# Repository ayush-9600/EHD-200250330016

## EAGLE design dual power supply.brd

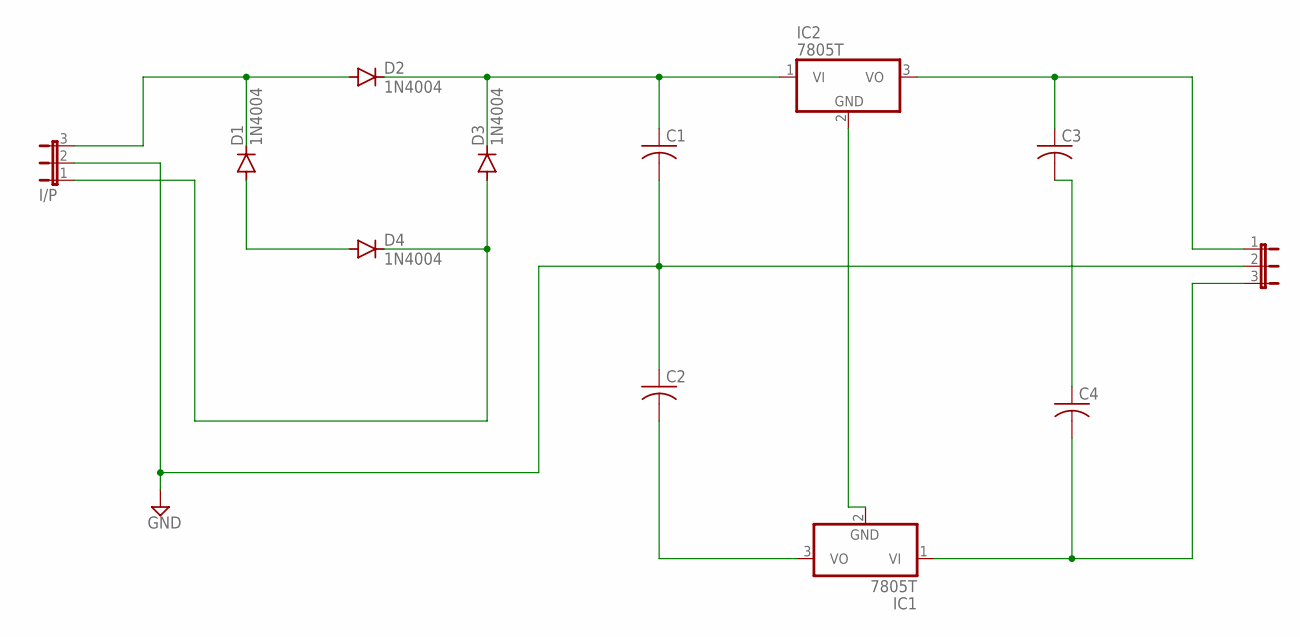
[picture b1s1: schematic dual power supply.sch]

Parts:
C1, C2, C3, C4: C-US025-024X044; C025-024X044
D1, D2, D3, D4: 1N4004; DO41-10
I/P: JP2E; JP2
IC1, IC2: 7805T; TO220H
O/P: JP2E; JP2

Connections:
GND: C1.2, C2.1, I/P.2, O/P.2
unnamed: D1.C, D2.A, I/P.3
unnamed: D1.A, D4.A
unnamed: C1.1, D2.C, D3.C, IC2.1 (VI)
unnamed: D3.A, D4.C, I/P.1
unnamed: IC1.2 (GND), IC2.2 (GND)
unnamed: C4.2, IC1.1 (VI), O/P.3
unnamed: C2.2, IC1.3 (VO)
unnamed: C3.1, IC2.3 (VO), O/P.1
unnamed: C3.2, C4.1

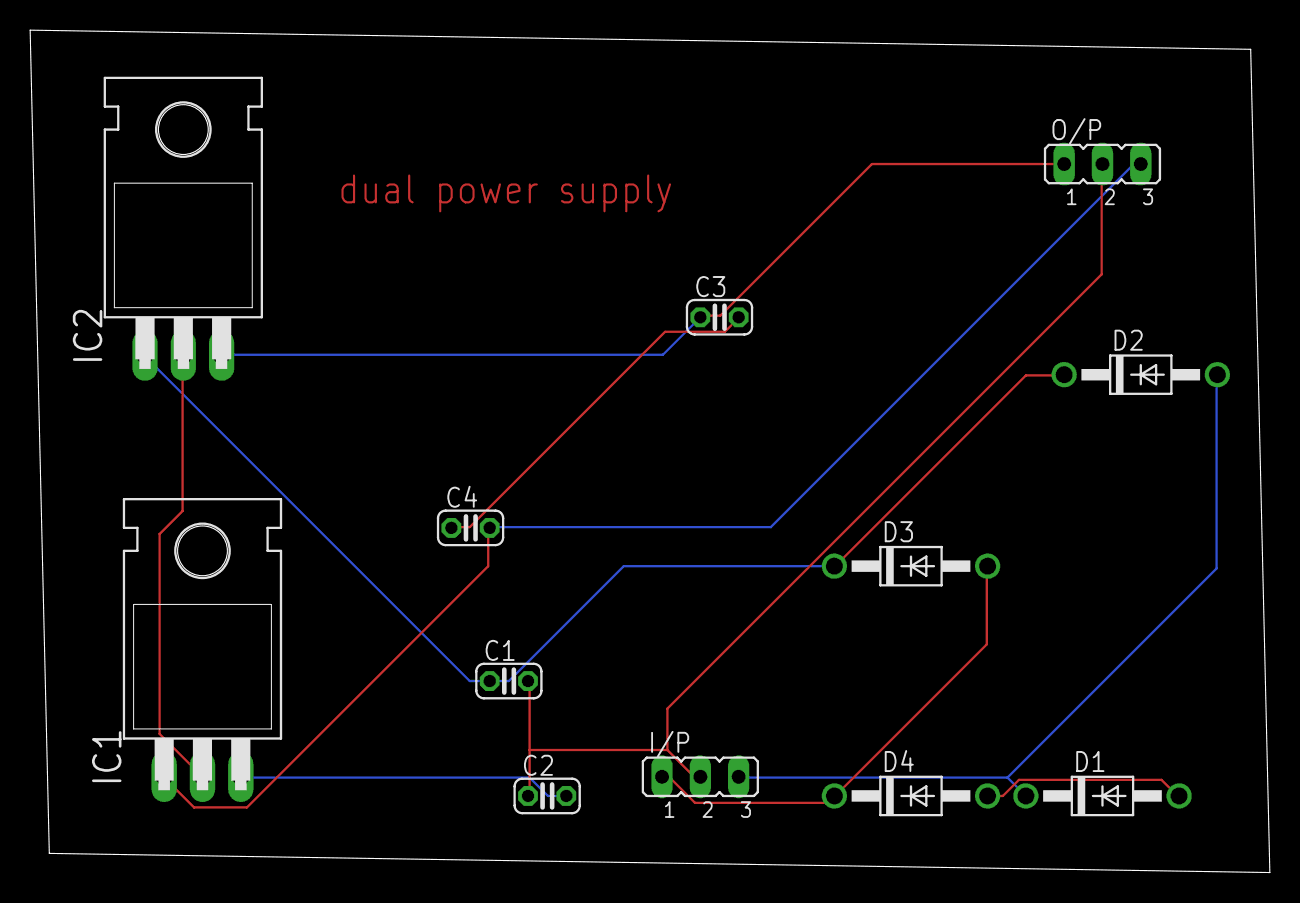
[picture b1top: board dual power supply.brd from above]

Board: 2 copper layers, 82.2 x 55.9 mm, 12 parts (0 on the bottom side), 10 nets.

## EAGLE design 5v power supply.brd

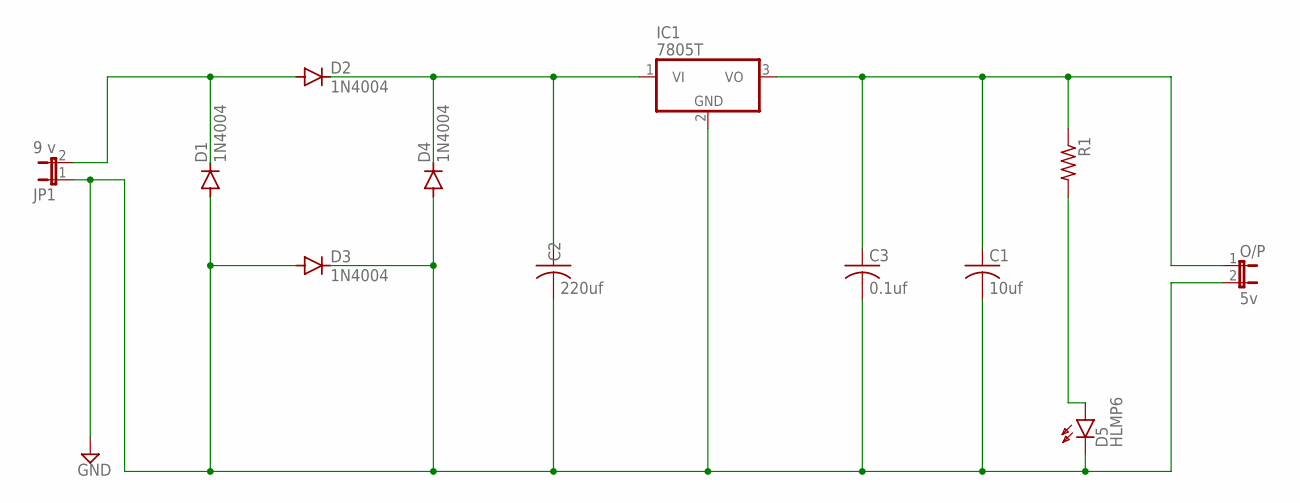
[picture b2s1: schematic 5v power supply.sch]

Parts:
C1: 10uf; C025-024X044
C2: 220uf; C025-024X044
C3: 0.1uf; C025-024X044
D1, D2, D3, D4: 1N4004; DO41-10
D5: HLMP6
IC1: 7805T; TO220H
JP1: 9 v; JP1
O/P: 5v; JP1
R1: R-US_0204/2V; 0204V

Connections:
GND: C1.2, C2.2, C3.2, D1.A, D3.A, D3.C, D4.A, D5.K, IC1.2 (GND), JP1.1, O/P.2
unnamed: D1.C, D2.A, JP1.2
unnamed: C2.1, D2.C, D4.C, IC1.1 (VI)
unnamed: C1.1, C3.1, IC1.3 (VO), O/P.1, R1.1
unnamed: D5.A, R1.2

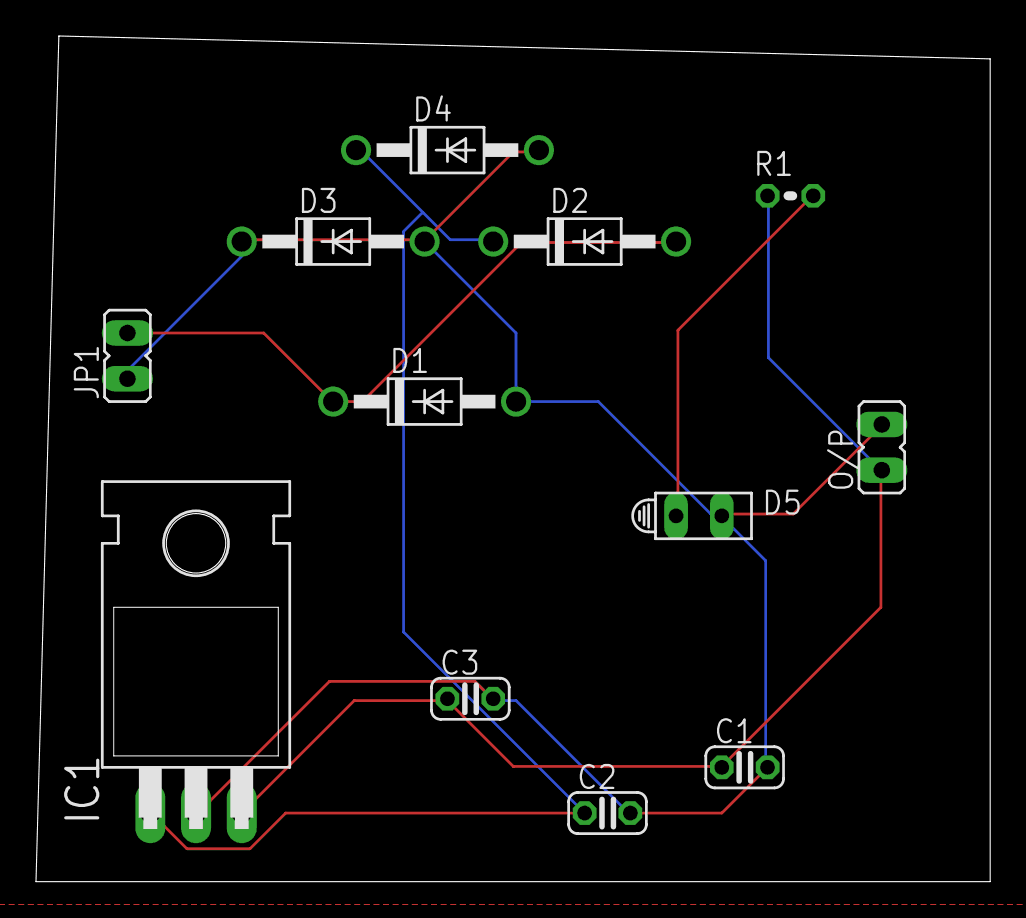
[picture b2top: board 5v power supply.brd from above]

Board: 2 copper layers, 53.0 x 47.0 mm, 12 parts (0 on the bottom side), 5 nets.
